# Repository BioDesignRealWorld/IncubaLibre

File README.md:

IncubaLibre
===========

A (hopefully) dirt cheap incubator circuit.

Parts
-----

(Approximate price)

* ATtiny85 (0.70)
* Relay (1)
* 5V regulator (0.5)
* P-channel MOSFET (0.6)

Discussions and Improvements
----------------------------

Discussions and improvement lists can be found on [hackpad](https://hackpad.com/Cheap-ass-incubator-z2wQQfcZajG).

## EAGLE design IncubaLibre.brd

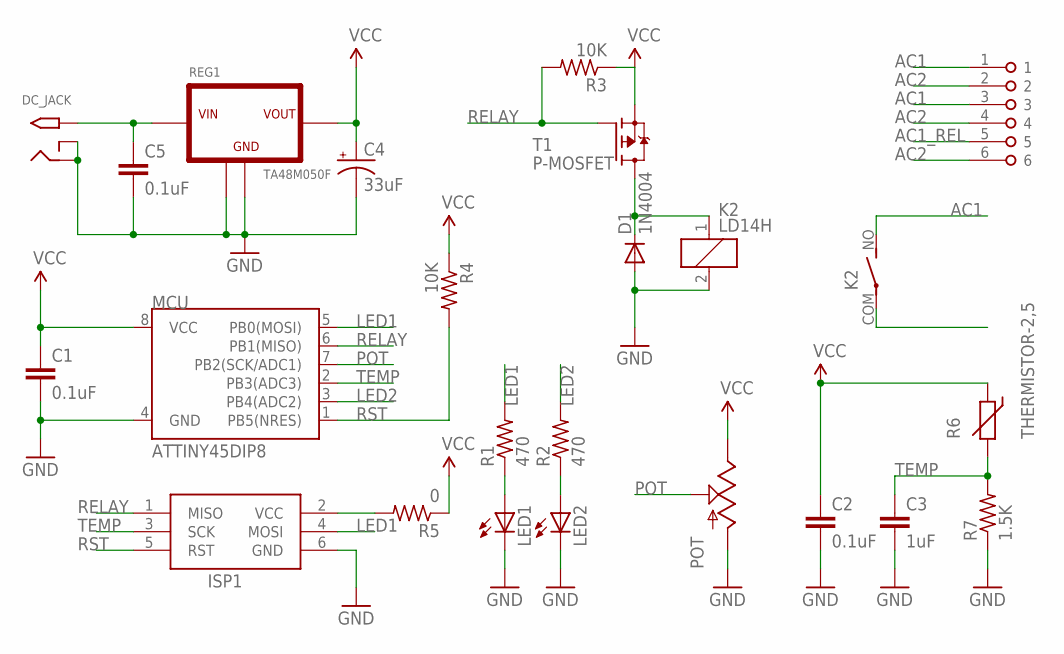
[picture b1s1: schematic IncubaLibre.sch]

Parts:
AC: TERMINAL-6; MBE-156
C1, C2, C5: 0.1uF; CAP-PTH-SMALL
C3: 1uF; CAP-PTH-SMALL
C4: 33uF; CPOL-RADIAL-10UF-25V
D1: 1N4004; DO41-10
DC_JACK: 2.1MMJACKTHM; PJ-102A
ISP1: AVRISP-6; AVRISP
K2: LD14H; LD
LED1, LED2: LED5MM
MCU: ATTINY45DIP8; DIP08
POT: POTTRIM; TRIM_POT
R1, R2: 470; 0204/7
R3, R4: 10K; 0204/7
R5: 0; 0204/7
R6: THERMISTOR-2,5; RS-2,5
R7: 1.5K; 0204/7
REG1: TA48M050F; TO-220
T1: P-MOSFET; TO92-

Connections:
AC1: AC.1, AC.3, K2.NO (S)
AC1_REL: AC.5, K2.COM
AC2: AC.2, AC.4, AC.6
GND: C1.2, C2.2, C3.2, C4.2 (-), C5.2, D1.A, DC_JACK.RING, DC_JACK.RING_SW, ISP1.6 (GND), K2.2, LED1.K (C), LED2.K (C), MCU.4 (GND), POT.3 (A), R7.1, REG1.CENTER (GND), REG1.THERMAL (GND)
LED1: ISP1.4 (MOSI), MCU.5 (PB0(MOSI)), R1.2
LED2: MCU.3 (PB4(ADC2)), R2.2
unnamed: ISP1.2 (VCC), R5.2
unnamed: LED1.A, R1.1
unnamed: LED2.A, R2.1
unnamed: C5.1, DC_JACK.TIP, REG1.LEFT (VIN)
POT: MCU.7 (PB2(SCK/ADC1)), POT.1 (S)
RELAY: ISP1.1 (MISO), MCU.6 (PB1(MISO)), R3.2, T1.2 (G)
RST: ISP1.5 (RST), MCU.1 (PB5(NRES)), R4.2
T1: D1.C, K2.1, T1.1 (D)
TEMP: C3.1, ISP1.3 (SCK), MCU.2 (PB3(ADC3)), R6.2, R7.2
VCC: C1.1, C2.1, C4.1 (+), MCU.8 (VCC), POT.2 (E), R3.1, R4.1, R5.1, R6.1, REG1.RIGHT (VOUT), T1.3 (S)

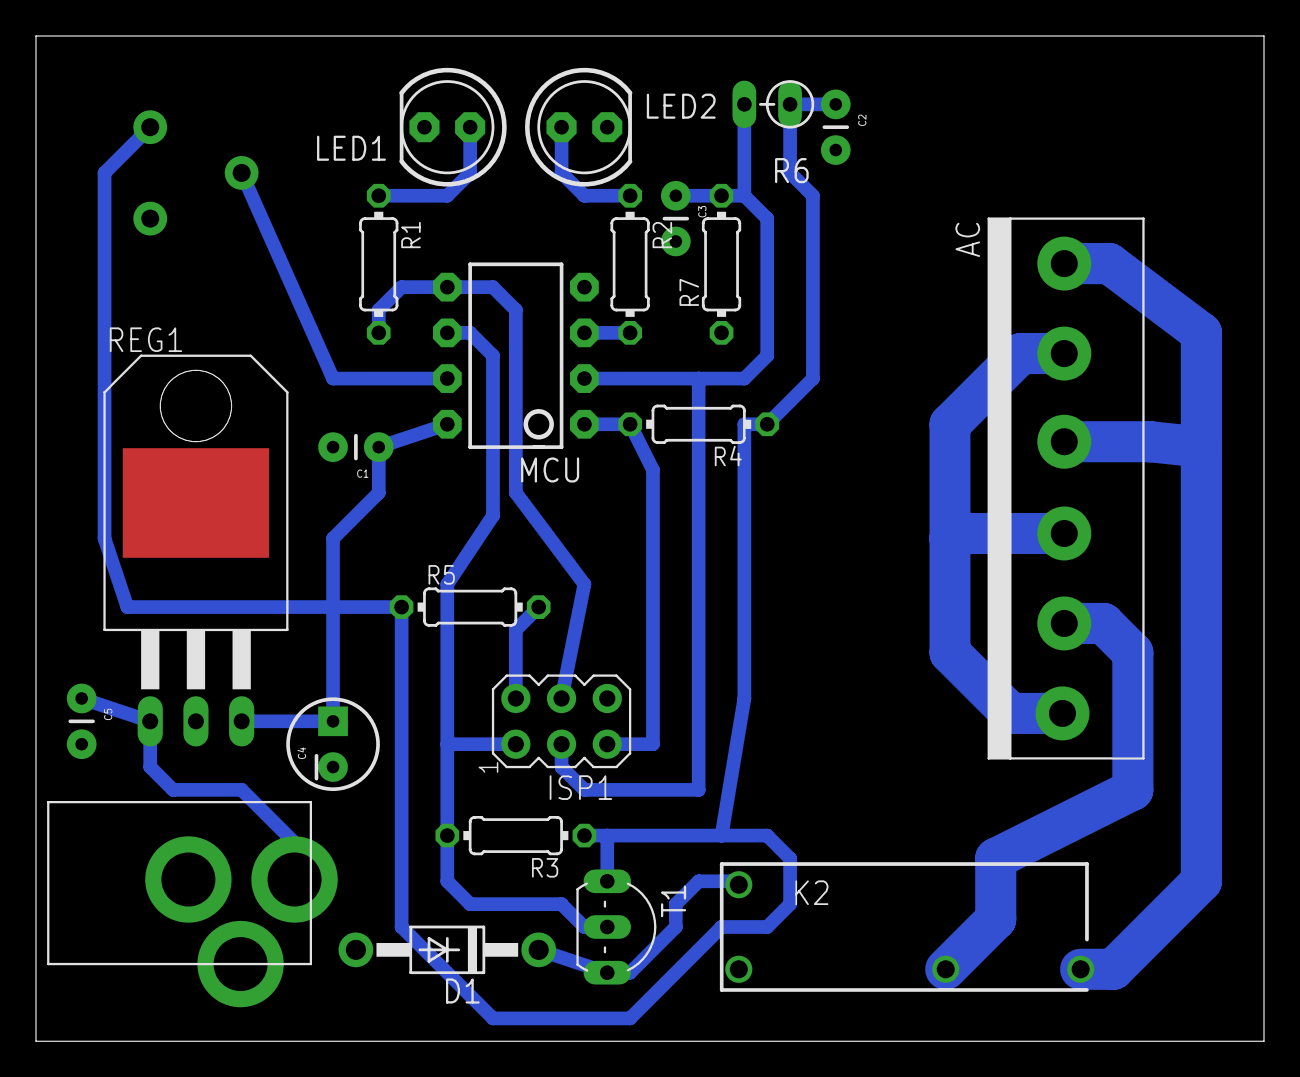
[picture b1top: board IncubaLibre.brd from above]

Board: 2 copper layers, 68.2 x 55.9 mm, 23 parts (0 on the bottom side), 16 nets.

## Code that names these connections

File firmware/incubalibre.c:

/*
* ----------------------------------------------------------------------------
* "THE BEER-WARE LICENSE" (Revision 42):
* <fakufaku@gmail.com> wrote this file. As long as you retain this notice you
* can do whatever you want with this stuff. If we meet some day, and you think
* this stuff is worth it, you can buy me a beer in return -- Robin Scheibler
* ----------------------------------------------------------------------------
*/

/*
 * IncubaLibre
 * ===========
 *
 * This is a cheap controller to regulate temperature in closed environment
 * using a consumer heating element such as a light bulb or a blow dryer.
 *
 * Control Loop Flow
 * -----------------
 *
 * The code uses TIMER1 as a slow PWM to switch a relay. 
 * The duty cycle of the relay is controlled by a PID loop.
 * The temperature is measured using a thermistor.
 *
 * The system clock of the ATtiny85 is left to the default 1MHz
 * and the prescaler of TIMER1 is set to clk/16834, which means
 * the loop period is ~4 seconds.
 *
 * Counter value ->
 * +---------------+------------------------------------------+
 * 0x0             OCR1A                                   0xFF
 * |               |                                          |
 * | Relay on      | Relay off (only when PWM on)             |
 * |               |                                          |
 * |               | On compare match interrupt               |
 * |               |   - measure trimpot                      |
 * |               |     - if trimpot != 0, start pwm         |
 * |               |     - else stop pwm                      |
 * |               |   - measure temperature                  |
 * |               |     - if incubator running recompute PID |
 * +---------------+------------------------------------------+
 *
 * Thermistor
 * ----------
 *
 * The thermistor was calibrated using a thermocouple and some hot water.
 * A look up table indexed on the ADC value is stored in the flash
 * memory.
 *
 */

#include <avr/io.h>
#include <avr/interrupt.h>
#include <avr/pgmspace.h>
#include <math.h>

// Allows to disable interrupt in some parts of the code
#define ENTER_CRIT()    {char volatile saved_sreg = SREG; cli()
#define LEAVE_CRIT()    SREG = saved_sreg;}

// Time interval is 1MHz/16384/256
#define TIME_INTERVAL 4.194304
#define TIME_INTERVAL_INV 0.2384186

// the state variable
#define PWM_ON 0
#define PWM_OFF 1
static uint8_t state = PWM_OFF;

// error when we consider set point is reached
#define TEMP_SET_ERROR 1.0

// measurements
uint8_t trimpot_val = 0;
float temperature_avg = 0.;
uint8_t temp_avg_n = 0;

// Temperature set point
float temperature_setPoints[4] = { 0.0, 37.5, 40.0, 45.0 };

// PID constants
float K_p = 10.;
float K_i = 0.5;
float K_d = 0.0;

// PID values
float error_previous = 0.;
float ITerm = 0.0;

// We limit PWM value to 4 from below to spare the relay
// and to 128 from above to avoid overheating of the incubator
#define PWM_MAX 200
#define PWM_MIN 6
uint8_t pwm_val = 0;

// Relay and LEDs macros
#define RELAY_ON()  PORTB &= ~(1 << PB1)
#define RELAY_OFF() PORTB |= (1 << PB1)
#define LED1_ON()   PORTB |= (1 << PB0)
#define LED1_OFF()  PORTB &= ~(1 << PB0)
#define LED2_ON()   PORTB |= (1 << PB4)
#define LED2_OFF()  PORTB &= ~(1 << PB4)

#define START_PWM_1A() TCCR1 |= (1 << PWM1A) | (1 << COM1A1) | (1 << COM1A0)
#define STOP_PWM_1A()  TCCR1 &= ~((1 << PWM1A) | (1 << COM1A1) | (1 << COM1A0))

// Look-up table of Thermistor values
const float therm_lut[] PROGMEM = { -66.89, -53.98, -47.36, -42.76, -39.19, -36.24, -33.71, -31.49, -29.51, -27.72, 
  -26.07, -24.55, -23.14, -21.81, -20.56, -19.37, -18.25, -17.17, -16.15, -15.17, 
  -14.22, -13.31, -12.43, -11.58, -10.76, -9.96, -9.18, -8.43, -7.69, -6.97, 
  -6.27, -5.59, -4.92, -4.26, -3.62, -2.99, -2.37, -1.77, -1.17, -0.59, 
  -0.01, 0.56, 1.12, 1.67, 2.21, 2.75, 3.27, 3.80, 4.31, 4.82, 
  5.32, 5.82, 6.31, 6.80, 7.28, 7.76, 8.23, 8.70, 9.16, 9.62, 
  10.08, 10.53, 10.98, 11.42, 11.86, 12.30, 12.74, 13.17, 13.60, 14.03, 
  14.45, 14.88, 15.30, 15.71, 16.13, 16.54, 16.95, 17.36, 17.77, 18.18, 
  18.58, 18.98, 19.38, 19.78, 20.18, 20.58, 20.98, 21.37, 21.76, 22.16, 
  22.55, 22.94, 23.33, 23.72, 24.11, 24.49, 24.88, 25.27, 25.65, 26.04, 
  26.42, 26.81, 27.19, 27.58, 27.96, 28.35, 28.73, 29.11, 29.50, 29.88, 
  30.26, 30.65, 31.03, 31.42, 31.80, 32.19, 32.57, 32.96, 33.34, 33.73, 
  34.12, 34.51, 34.89, 35.28, 35.67, 36.06, 36.46, 36.85, 37.24, 37.64, 
  38.03, 38.43, 38.83, 39.23, 39.63, 40.03, 40.44, 40.84, 41.25, 41.66, 
  42.07, 42.48, 42.89, 43.31, 43.72, 44.14, 44.56, 44.99, 45.41, 45.84, 
  46.27, 46.70, 47.14, 47.57, 48.01, 48.46, 48.90, 49.35, 49.80, 50.26, 
  50.71, 51.17, 51.64, 52.11, 52.58, 53.05, 53.53, 54.01, 54.50, 54.99, 
  55.49, 55.99, 56.49, 57.00, 57.51, 58.03, 58.55, 59.08, 59.62, 60.16, 
  60.70, 61.26, 61.82, 62.38, 62.95, 63.53, 64.12, 64.71, 65.31, 65.92, 
  66.54, 67.16, 67.79, 68.44, 69.09, 69.75, 70.43, 71.11, 71.80, 72.51, 
  73.23, 73.96, 74.70, 75.46, 76.23, 77.02, 77.82, 78.64, 79.47, 80.32, 
  81.20, 82.09, 83.00, 83.93, 84.89, 85.87, 86.87, 87.90, 88.96, 90.06, 
  91.18, 92.34, 93.53, 94.76, 96.04, 97.35, 98.72, 100.14, 101.61, 103.14, 
  104.74, 106.41, 108.16, 110.00, 111.92, 113.95, 116.10, 118.38, 120.80, 123.39, 
  126.16, 129.15, 132.39, 135.93, 139.81, 144.12, 148.94, 154.41, 160.71, 168.12, 
  177.05, 188.24, 202.99, 224.20, 260.13, 630.92 };

void measure_temperature()
{
  /* Measure Temperature */

  // select ADC3 single-ended channel
  // Left adjust to have 8 upper bits in the upper register
  ADMUX = (1 << MUX1) | (1 << MUX0) | (1 << ADLAR);

  // start conversion
  ADCSRA |= (1 << ADSC);

  // wait for conversion to finish
  while (ADCSRA & (1 << ADSC))
    ;

  // We only use the 8 upper bit of the ADC value
  // for the temperature
  uint8_t high = ADCH;

  // average the temperature measurement
  temperature_avg = pgm_read_float(&(therm_lut[high]));
  //temperature_avg = 0.8*temperature_avg + 0.2*pgm_read_float(&(therm_lut[high]));
}

void measure_trimpot()
{
  /* Measure the trimpot value */
  
  // select ADC1 single-ended channel
  // Left adjust to have 8 upper bits in the upper register
  ADMUX = (1 << MUX0) | (1 << ADLAR);

  // start conversion
  ADCSRA |= (1 << ADSC);

  // wait for conversion to finish
  while (ADCSRA & (1 << ADSC))
    ;

  // We only use few upper bit of the ADC value
  // for the trimpot value
  uint8_t high = ADCH;
  trimpot_val = high >> 6;
}

void PID_compute()
{
  /*Compute all the working error variables*/
  float error = 37.5 - temperature_avg;

  // turn the LED2 on if we are close to set temperature
  if (fabs(error) < TEMP_SET_ERROR)
    LED2_ON();
  else
    LED2_OFF();

  // integral term (using trapeze method)
  ITerm += (K_i * TIME_INTERVAL * (error + error_previous)*0.5);
  if (ITerm > PWM_MAX) 
    ITerm = PWM_MAX;
  else if (ITerm < PWM_MIN) 
  {
    ITerm = PWM_MIN;
  }

  // differential term
  float dInput = (error - error_previous) * TIME_INTERVAL_INV;

  /*Compute PID Output*/
  float output = K_p * error + ITerm + K_d * dInput;

  // set PWM value
  if (output > PWM_MAX)
    pwm_val = PWM_MAX;
  else if (output < PWM_MIN) 
    pwm_val = 0.;
  else
    pwm_val = (uint8_t)output;

  /*Remember some variables for next time*/
  error_previous = error;
}

// Here we turn the relay off
SIGNAL(TIMER1_COMPA_vect)
{
  measure_trimpot();
  measure_temperature();
  
  if (trimpot_val > 0)
  {
    if (state == PWM_OFF)
    {
      START_PWM_1A();
      state = PWM_ON;

      LED1_ON();
    }

    // do the PID magic
    PID_compute();
  }
  else
  {
    if (state == PWM_ON)
    {
      STOP_PWM_1A();
      state = PWM_OFF;

      RELAY_OFF();

      LED1_OFF();
      pwm_val = 0;
      ITerm = 0.0;
      error_previous = 0.0;
    }
  }
}

// The timer overflow interrupt routine
SIGNAL(TIMER1_OVF_vect)
{
  // set pwm duty cycle to value computed by PID
  OCR1A = pwm_val;
}

int main()
{
  int i;

  // enable interrupts
  sei();

  // ADC setting, enabled, prescaled clk/16
  ADCSRA = (1 << ADEN) | (1 << ADPS2);

  // set up timer 1 as system clock
  TCNT1 = 0x0;            // counter at zero
  TIMSK |= (1 << TOIE1) | (1 << OCIE1A);   // set the overflow interrupt
  TCCR1 = (1 << CS13) | (1 << CS12) | (1 << CS11) | (1 << CS10); // T1 clock to clk/16384

  // configure PB1 to switch relay
  // configure PB0 and PB4 for the two LEDs
  DDRB = (1 << PB1) | (1 << PB0) | (1 << PB4);
  RELAY_OFF();
  LED1_OFF();
  LED2_OFF();

  // The infinite loop
  while (1)
  {

  }

}

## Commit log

2014-04-25 Added README and rough part cost of most expensive components.
2014-08-20 Initial buggy firmware code.
2014-08-25 Added thermistor calibration script.
2014-08-25 Removed old python script. Renamed most recent calibration data file.
2014-08-27 Temperature measurement now working correctly. PID seems to work more or less. Still buggy.
2014-09-04 Cleaned and debugged incubalibre.c. Now the incubator seems to be working (from the software pov).
2014-09-04 Added gitignore file.
